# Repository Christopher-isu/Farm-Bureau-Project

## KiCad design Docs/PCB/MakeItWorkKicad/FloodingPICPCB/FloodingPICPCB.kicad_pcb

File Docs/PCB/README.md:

# Farm-Bureau-Project
5th semester final project

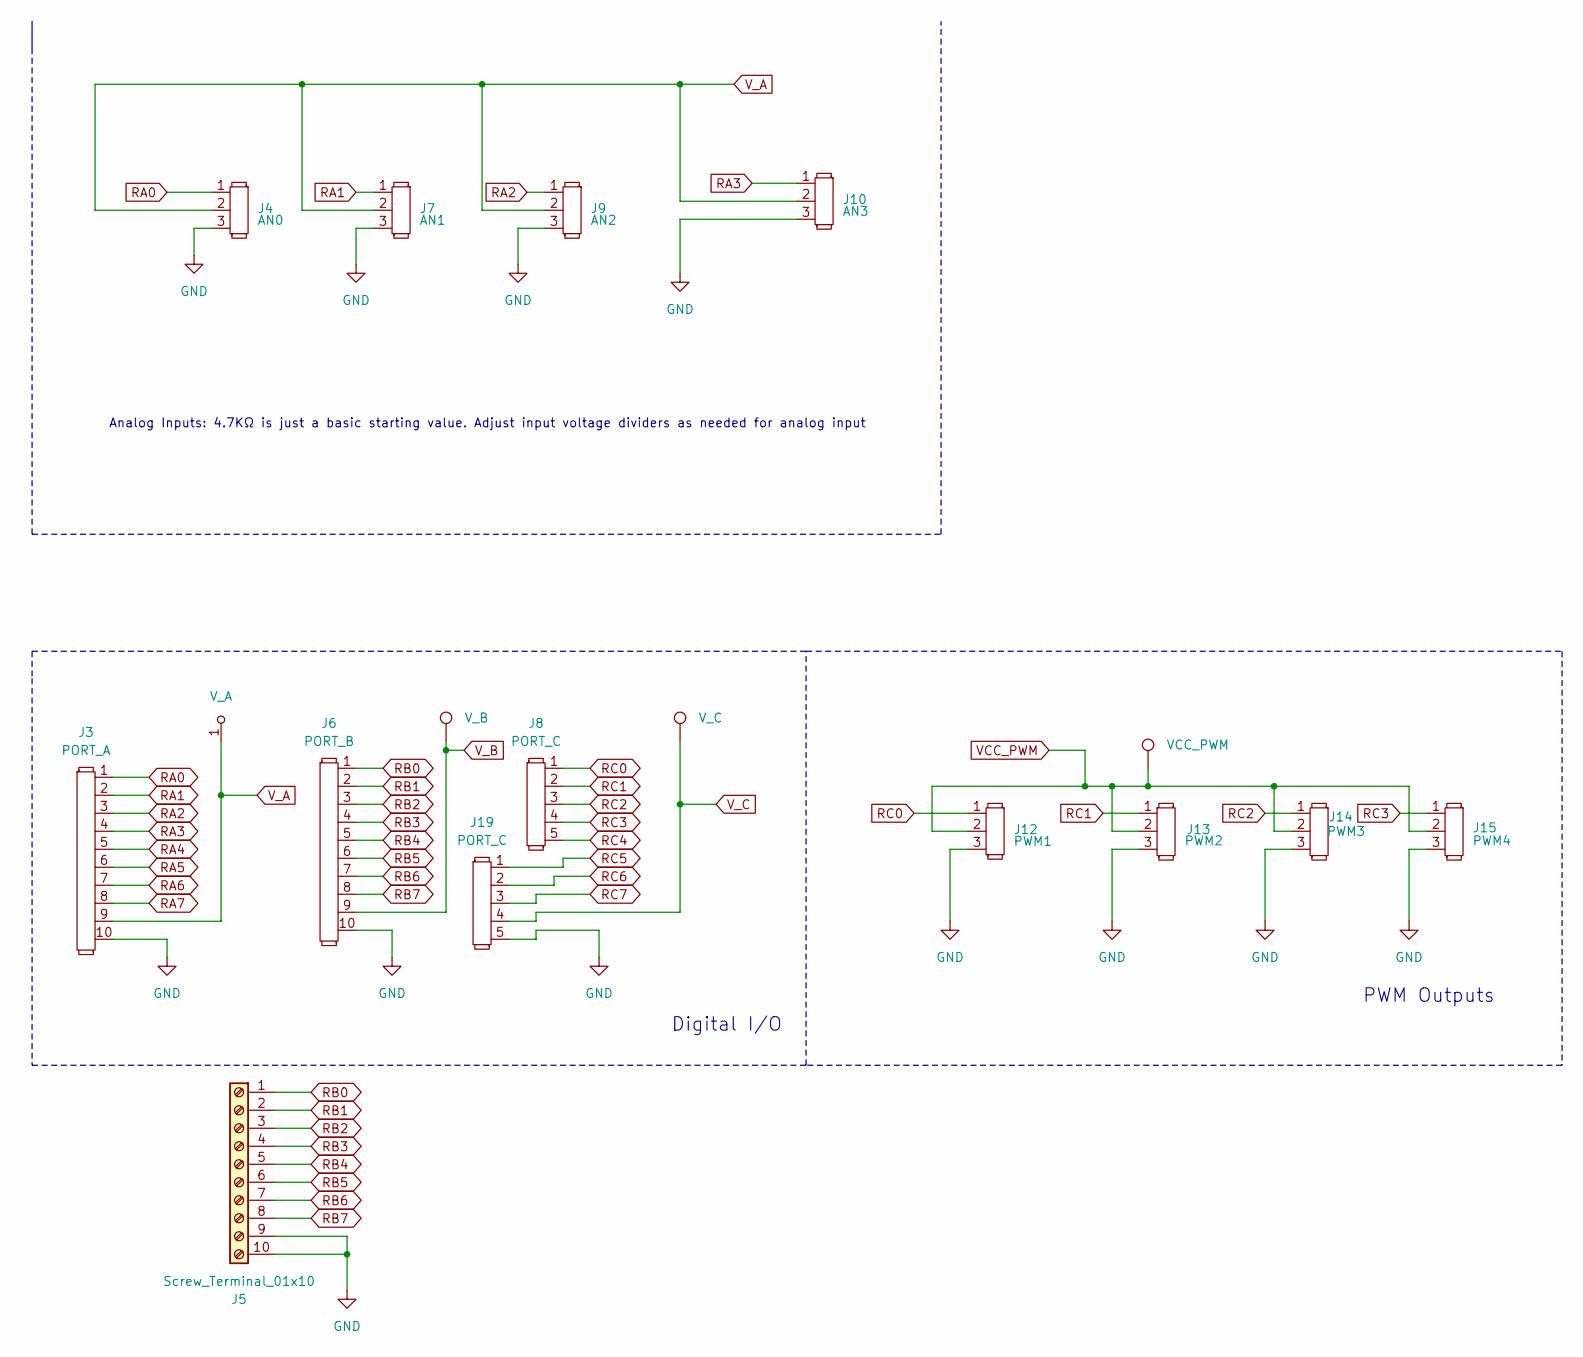
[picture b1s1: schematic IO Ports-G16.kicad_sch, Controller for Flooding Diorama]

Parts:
J3: PORT_A; 1991341
J4: AN0; PinHeader_1x03_P2.54mm_Vertical
J5: Screw_Terminal_01x10; 1991341
J6: PORT_B; PinHeader_1x10_P2.54mm_Vertical
J7: AN1; PinHeader_1x03_P2.54mm_Vertical
J8, J19: PORT_C; 5PositionScrew
J9: AN2; PinHeader_1x03_P2.54mm_Vertical
J10: AN3; PinHeader_1x03_P2.54mm_Vertical
J12: PWM1; PinHeader_1x03_P2.54mm_Vertical
J13: PWM2; PinHeader_1x03_P2.54mm_Vertical
J14: PWM3; PinHeader_1x03_P2.54mm_Vertical
J15: PWM4; PinHeader_1x03_P2.54mm_Vertical

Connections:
+3.3V: J3.9, J4.2, J6.9, J7.2, J9.2, J10.2, J12.2, J13.2, J14.2, J15.2, J19.4; also elsewhere on the board
GND: J3.10, J4.3, J5.9, J5.10, J6.10, J7.3, J9.3, J10.3, J12.3, J13.3, J14.3, J15.3, J19.5; also elsewhere on the board
RA0: J3.1, J4.1; also elsewhere on the board
RA1: J3.2, J7.1; also elsewhere on the board
RA2: J3.3, J9.1; also elsewhere on the board
RA3: J3.4, J10.1; also elsewhere on the board
RA4: J3.5; also elsewhere on the board
RA5: J3.6; also elsewhere on the board
RA6: J3.7; also elsewhere on the board
RA7: J3.8; also elsewhere on the board
RB0: J5.1, J6.1; also elsewhere on the board
RB1: J5.2, J6.2; also elsewhere on the board
RB2: J5.3, J6.3; also elsewhere on the board
RB3: J5.4, J6.4; also elsewhere on the board
RB4: J5.5, J6.5; also elsewhere on the board
RB5: J5.6, J6.6; also elsewhere on the board
RB6: J5.7, J6.7; also elsewhere on the board
RB7: J5.8, J6.8; also elsewhere on the board
RC0: J8.1, J12.1; also elsewhere on the board
RC1: J8.2, J13.1; also elsewhere on the board
RC2: J8.3, J14.1; also elsewhere on the board
RC3: J8.4, J15.1; also elsewhere on the board
RC4: J8.5; also elsewhere on the board
RC5: J19.1; also elsewhere on the board
RC6: J19.2; also elsewhere on the board
RC7: J19.3; also elsewhere on the board

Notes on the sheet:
Analog Inputs: 4.7KΩ is just a basic starting value. Adjust input voltage dividers as needed for analog input
PWM Outputs
Digital I/O

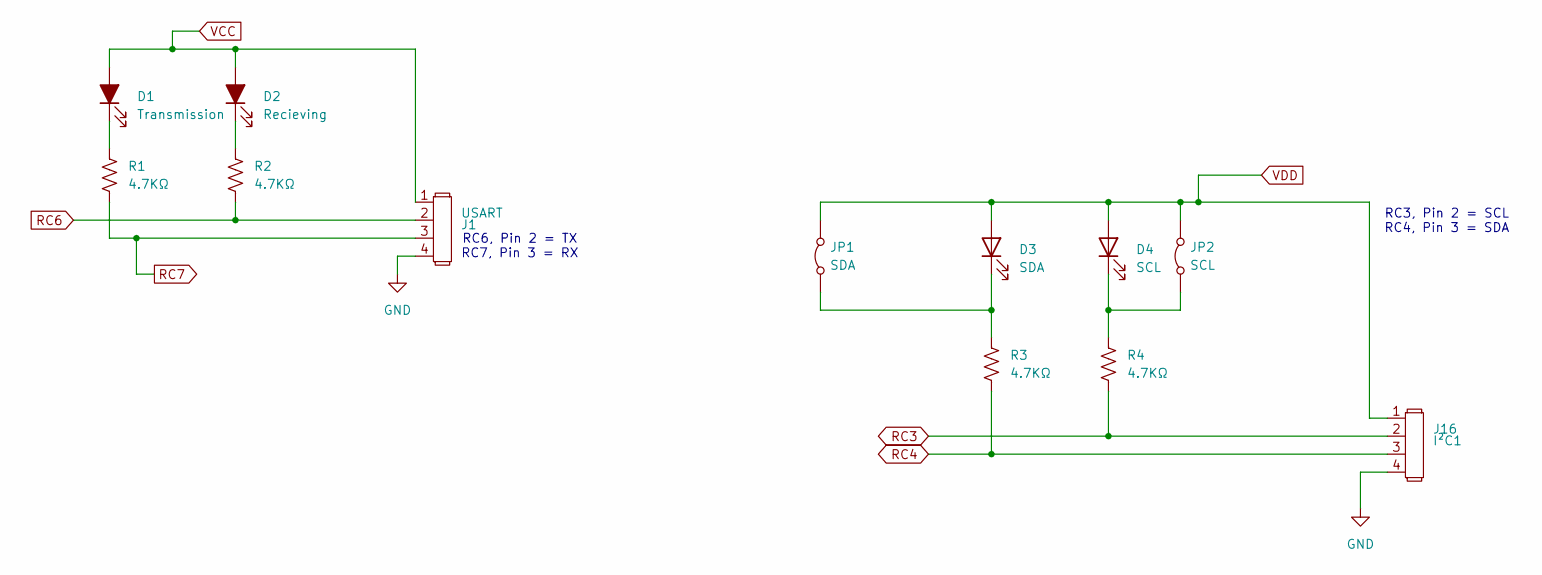
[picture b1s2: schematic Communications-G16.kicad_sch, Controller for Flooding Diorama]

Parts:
D1: Transmission; D_0805_2012Metric_Pad1.15x1.40mm_HandSolder
D2: Recieving; D_0805_2012Metric_Pad1.15x1.40mm_HandSolder
D3: SDA; D_0805_2012Metric_Pad1.15x1.40mm_HandSolder
D4: SCL; D_0805_2012Metric_Pad1.15x1.40mm_HandSolder
I²C1: J16; PinHeader_1x04_P2.54mm_Vertical
J1: USART; PinHeader_1x04_P2.54mm_Vertical
JP1: SDA; PinHeader_1x02_P2.54mm_Vertical
JP2: SCL; PinHeader_1x03_P2.54mm_Vertical
R1, R2, R3, R4: 4.7KΩ; R_0805_2012Metric_Pad1.20x1.40mm_HandSolder

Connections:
+3.3V: D1.2 (A), D2.2 (A), D3.2 (A), D4.2 (A), I²C1.1, J1.1, JP1.2 (B), JP2.2 (B); also elsewhere on the board
GND: I²C1.4, J1.4; also elsewhere on the board
unnamed: D1.1 (K), R1.1
unnamed: D2.1 (K), R2.1
unnamed: D3.1 (K), JP1.1 (A), R3.1
unnamed: D4.1 (K), JP2.1 (A), R4.1
RC3: I²C1.2, R4.2; also elsewhere on the board
RC4: I²C1.3, R3.2; also elsewhere on the board
RC6: J1.2, R2.2; also elsewhere on the board
RC7: J1.3, R1.2; also elsewhere on the board

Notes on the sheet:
RC6, Pin 2 = TX RC7, Pin 3 = RX
RC3, Pin 2 = SCL RC4, Pin 3 = SDA

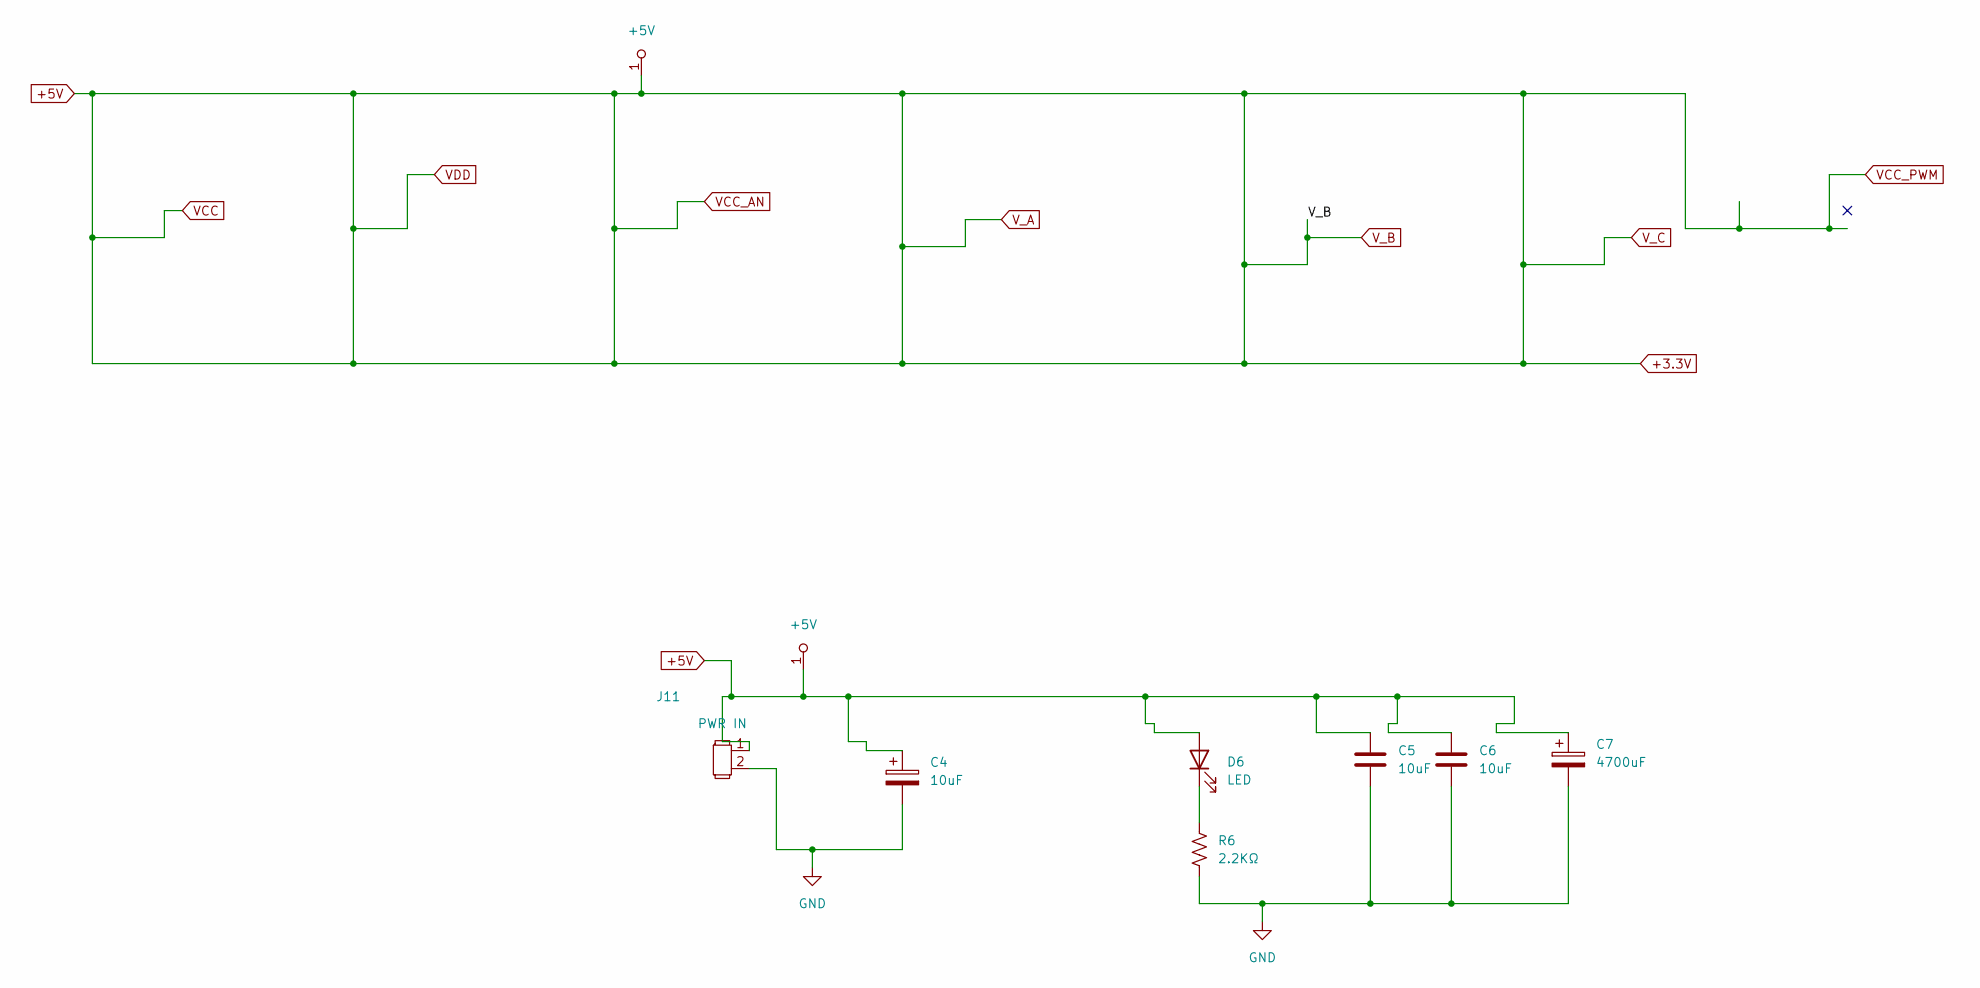
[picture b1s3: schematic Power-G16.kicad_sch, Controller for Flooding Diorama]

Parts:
C4, C5, C6: 10uF; C_0805_2012Metric_Pad1.18x1.45mm_HandSolder
C7: 4700uF; CP_Radial_D18.0mm_P7.50mm
D6: LED; D_0805_2012Metric_Pad1.15x1.40mm_HandSolder
J11: PWR IN; RightAngle2Molex
R6: 2.2KΩ; R_0805_2012Metric_Pad1.20x1.40mm_HandSolder

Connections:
+3.3V: C4.1, C5.1, C6.1, C7.1, D6.2 (A), J11.1; also elsewhere on the board
GND: C4.2, C5.2, C6.2, C7.2, J11.2, R6.2; also elsewhere on the board
unnamed: D6.1 (K), R6.1

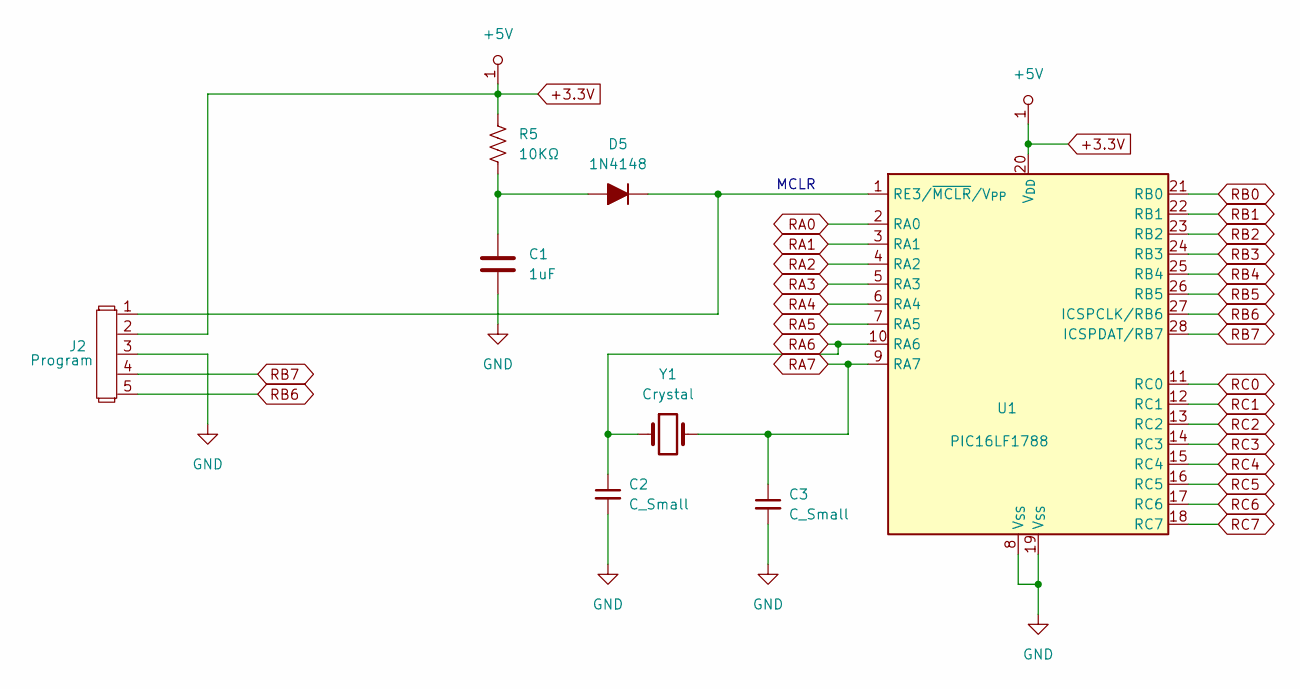
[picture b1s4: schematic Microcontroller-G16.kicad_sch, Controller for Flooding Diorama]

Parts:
C1: 1uF; C_0805_2012Metric_Pad1.18x1.45mm_HandSolder
C2, C3: C_Small; C_0805_2012Metric_Pad1.18x1.45mm_HandSolder
D5: 1N4148; D_0805_2012Metric_Pad1.15x1.40mm_HandSolder
J2: Program; PinHeader_1x05_P2.54mm_Vertical
R5: 10KΩ; R_0805_2012Metric_Pad1.20x1.40mm_HandSolder
U1: PIC16LF1788; PIC16SurfaceUseThis
Y1: Crystal; Crystal_HC49-U_Vertical

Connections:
+3.3V: J2.2, R5.1, U1.20 (V_{DD}); also elsewhere on the board
GND: C1.2, C2.2, C3.2, J2.3, U1.8 (V_{SS}), U1.19 (V_{SS}); also elsewhere on the board
unnamed: C1.1, D5.2 (A), R5.2
unnamed: D5.1 (K), J2.1, U1.1 (RE3/~MCLR/V_{PP})
RA0: U1.2 (RA0); also elsewhere on the board
RA1: U1.3 (RA1); also elsewhere on the board
RA2: U1.4 (RA2); also elsewhere on the board
RA3: U1.5 (RA3); also elsewhere on the board
RA4: U1.6 (RA4); also elsewhere on the board
RA5: U1.7 (RA5); also elsewhere on the board
RA6: C2.1, U1.10 (RA6), Y1.1; also elsewhere on the board
RA7: C3.1, U1.9 (RA7), Y1.2; also elsewhere on the board
RB0: U1.21 (RB0); also elsewhere on the board
RB1: U1.22 (RB1); also elsewhere on the board
RB2: U1.23 (RB2); also elsewhere on the board
RB3: U1.24 (RB3); also elsewhere on the board
RB4: U1.25 (RB4); also elsewhere on the board
RB5: U1.26 (RB5); also elsewhere on the board
RB6: J2.5, U1.27 (ICSPCLK/RB6); also elsewhere on the board
RB7: J2.4, U1.28 (ICSPDAT/RB7); also elsewhere on the board
RC0: U1.11 (RC0); also elsewhere on the board
RC1: U1.12 (RC1); also elsewhere on the board
RC2: U1.13 (RC2); also elsewhere on the board
RC3: U1.14 (RC3); also elsewhere on the board
RC4: U1.15 (RC4); also elsewhere on the board
RC5: U1.16 (RC5); also elsewhere on the board
RC6: U1.17 (RC6); also elsewhere on the board
RC7: U1.18 (RC7); also elsewhere on the board

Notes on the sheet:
MCLR

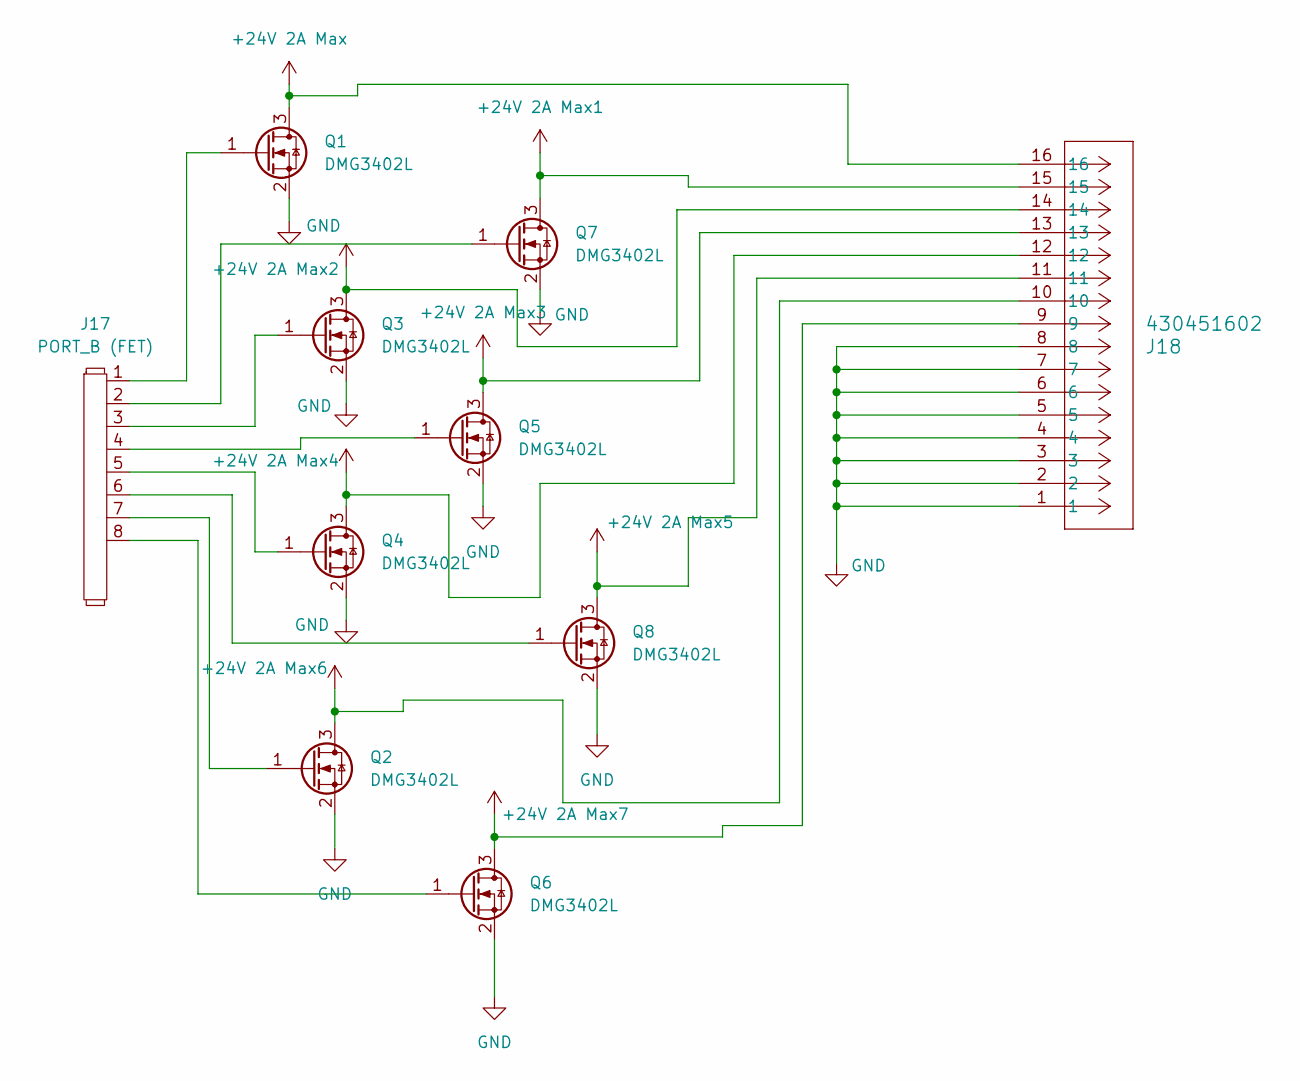
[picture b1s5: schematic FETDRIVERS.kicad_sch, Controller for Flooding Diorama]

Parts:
J17: PORT_B (FET); PinHeader_1x08_P2.54mm_Vertical
J18: 430451602; MolexBig
Q1, Q2, Q3, Q4, Q5, Q6, Q7, Q8: DMG3402L; SOT-23

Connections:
+24V 2A Max: J18.16, Q1.3 (D)
+24V 2A Max1: J18.15, Q7.3 (D)
+24V 2A Max2: J18.14, Q3.3 (D)
+24V 2A Max3: J18.13, Q5.3 (D)
+24V 2A Max4: J18.12, Q4.3 (D)
+24V 2A Max5: J18.11, Q8.3 (D)
+24V 2A Max6: J18.10, Q2.3 (D)
+24V 2A Max7: J18.9, Q6.3 (D)
GND: J18.1, J18.2, J18.3, J18.4, J18.5, J18.6, J18.7, J18.8, Q1.2 (S), Q2.2 (S), Q3.2 (S), Q4.2 (S), Q5.2 (S), Q6.2 (S), Q7.2 (S), Q8.2 (S); also elsewhere on the board
unnamed: J17.1, Q1.1 (G)
unnamed: J17.7, Q2.1 (G)
unnamed: J17.3, Q3.1 (G)
unnamed: J17.5, Q4.1 (G)
unnamed: J17.4, Q5.1 (G)
unnamed: J17.8, Q6.1 (G)
unnamed: J17.2, Q7.1 (G)
unnamed: J17.6, Q8.1 (G)

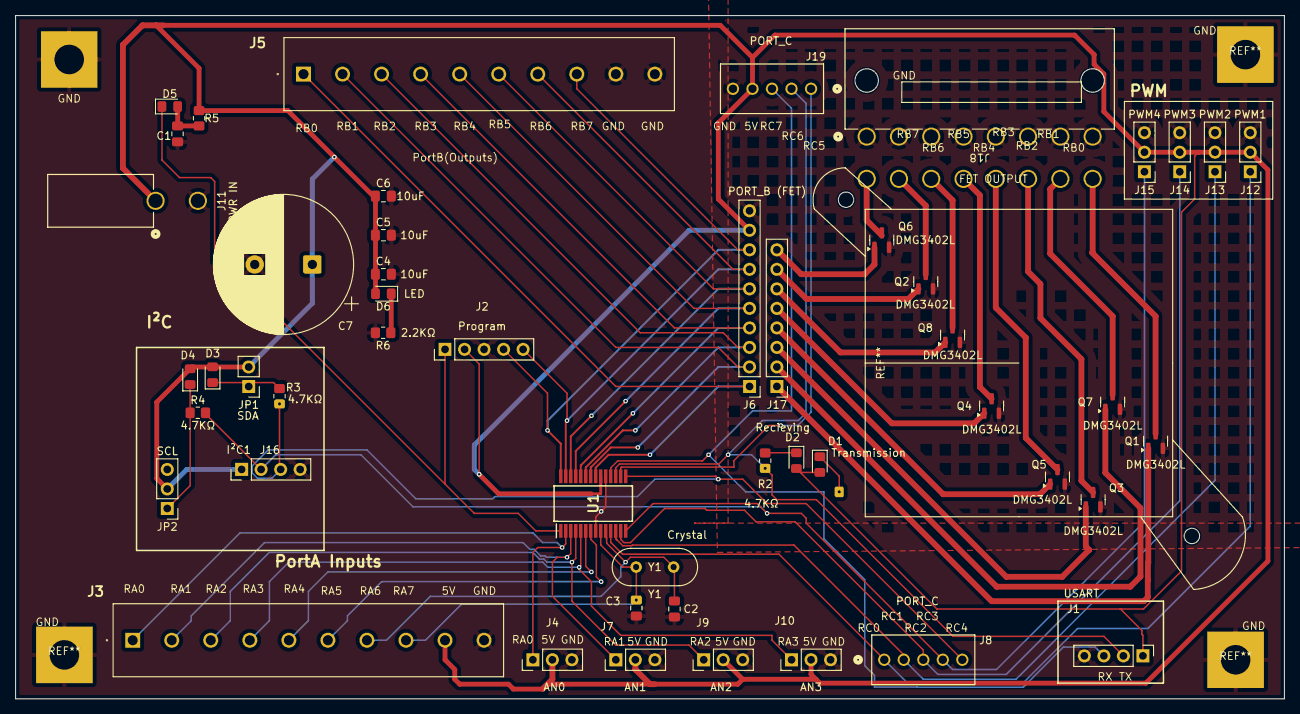
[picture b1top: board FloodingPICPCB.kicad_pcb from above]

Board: 2 copper layers, 165.1 x 88.9 mm, 51 parts (1 on the bottom side), 49 nets.

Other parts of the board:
GND: MountingHole

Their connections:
GND: GND.1; also elsewhere on the board

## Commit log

2025-11-19 Added an IO block diagram - v1
2025-12-05 add Code and Docs directories
2025-12-05 Add Hello.
2025-12-07 updated parts list
2025-12-08 added my project tracker
2025-12-10 Added C code for the PIC16F1788 for the watershed project.
2025-12-11 Near finalized code was added.
2025-12-11 Updated PCB design. Molex updated. Programming pins in new spot.
2025-12-16 updated the tracker for week 5
2025-12-19 final week uploads
2025-12-19 final update for this semester
